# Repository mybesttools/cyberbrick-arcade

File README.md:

# ESP32-C3 Controller Firmware

This project targets **ESP32-C3 BLE gamepad mode** by default.

The board advertises as `ESP32-C3 Arcade` and pairs directly with RetroPie over Bluetooth.

It also includes an optional tiny OLED status display (SSD1306 I2C) showing:

- boot status
- advertising / connected state
- live axis and button activity

## BLE and USB support

Yes, both are supported from the same codebase:

- BLE gamepad mode on ESP32-C3 (`esp32c3_esp32c3_ble`)
- USB serial bridge mode on ESP32-C3 (`esp32c3_esp32c3_usbserial`)

Note: ESP32-C3 does not expose native USB HID gamepad device mode in this project.
USB mode here is CDC serial output for a Pi-side bridge.

## Project layout

- `src/main.cpp`: controller firmware (BLE + USB HID + serial bridge modes)
- `include/pinmap.h`: joystick/button mapping and calibration
- `platformio.ini`: PlatformIO build config
- `tools/flash_our_firmware.sh`: upload helper for default ESP32-C3 BLE env

## Pinouts

### Config B — single joystick, direct GPIO buttons (default)

Environments: `esp32c3_esp32c3_ble`, `esp32c3_esp32c3_usbserial`

**Joystick** (analog, connect to 3.3 V, GND, and wiper):

| Signal  | GPIO  | Arduino pin |
|---------|-------|-------------|
| JOY X   | GPIO0 | A0          |
| JOY Y   | GPIO1 | A1          |

**Buttons** (active LOW — wire between GPIO pin and GND, internal pull-up enabled):

| Button | GPIO |
|--------|------|
| A      | 2    |
| B      | 3    |
| X      | 4    |
| Y      | 5    |
| L      | 6    |
| R      | 7    |
| START  | 9    |
| SELECT | 10   |
| HOTKEY | 20   |
| COIN   | 21   |

**OLED status display** (I2C, shared with Config A):

| Signal | GPIO |
|--------|------|
| SDA    | 5    |
| SCL    | 6    |

> Note: GPIO5/6 are shared between the OLED and button Y/L in Config B.
> If the display is connected, remove buttons Y and L from the `BUTTON_PINS[]`
> array in `include/pinmap.h`, or remap them to unused GPIOs.

---

### Config A — dual joystick, MCP23017 expander board

Environments: `esp32c3_ble_mcp`

All buttons are wired to the MCP23017 I/O expander (no direct GPIO buttons).
The MCP23017 connects over I2C with A0/A1/A2 address pins all tied to GND
(address `0x20`).

**Joysticks** (analog, connect to 3.3 V, GND, and wiper):

| Signal       | GPIO  | Arduino pin | Role                  |
|--------------|-------|-------------|-----------------------|
| Left JOY X   | GPIO0 | A0          | Hat switch            |
| Left JOY Y   | GPIO1 | A1          | Hat switch            |
| Right JOY X  | GPIO2 | A2          | BLE Rx axis           |
| Right JOY Y  | GPIO3 | A3          | BLE Ry axis           |

**I2C bus** (MCP23017 + OLED share the same bus):

| Signal | GPIO | Connected to         |
|--------|------|----------------------|
| SDA    | 5    | MCP23017 SDA, OLED SDA |
| SCL    | 6    | MCP23017 SCL, OLED SCL |

**MCP23017 button mapping** (active LOW — wire each button between the
MCP pin and GND; internal pull-ups are enabled by firmware):

| MCP pin | Board label | Button | Notes |
|---------|-------------|--------|-------|
| GPA0    | A0          | D-pad Up    | ✓ wired |
| GPA1    | A1          | D-pad Left  | ✓ wired |
| GPA2    | A2          | D-pad Right | ✓ wired |
| GPA3    | A3          | D-pad Down  | ✓ wired |
| GPA4    | A4          | L shoulder  | wire here |
| GPA5    | A5          | R shoulder  | wire here |
| GPA6    | A6          | Start       | wire here |
| GPA7    | A7          | Select      | wire here |
| GPB0    | B0          | Hotkey      | wire here |
| GPB1    | B1          | Coin        | wire here |
| GPB2    | B2          | R3 (right joystick click) | ✓ wired |
| GPB3    | B3          | L3 (left joystick click)  | ✓ wired |
| GPB4    | B4          | A / Cross ✕   (Down)  | ✓ wired |
| GPB5    | B5          | Y / Triangle △ (Up)   | ✓ wired |
| GPB6    | B6          | B / Circle ○  (Right) | ✓ wired |
| GPB7    | B7          | X / Square □  (Left)  | ✓ wired |

## Optional tiny OLED display

The BLE environment enables status output (`ESP32C3_STATUS_OLED`).

For ABrobot ESP32-C3 OLED boards, the onboard 0.42" display is a 72x40 pixel
OLED driven over I2C on GPIO5 (SDA) / GPIO6 (SCL).

**Reference article:**
[ESP32-C3 0.42" OLED — emalliab](https://emalliab.wordpress.com/2025/02/12/esp32-c3-0-42-oled/)

Key findings from debugging:
- Board I2C address may be **0x3C** or **0x3D** depending on variant — firmware probes both.
- Display controller may be SSD1306 or SH1106 — both U8g2 drivers are included.
- `Wire.begin()` with no arguments on ESP32-C3 defaults to GPIO8/GPIO9, which
  conflicts with the onboard LED on GPIO8. Always pass explicit SDA/SCL pins.
- The article uses `U8G2_SSD1306_72X40_ER_F_HW_I2C` which works without offset.
  The `U8G2_SSD1306_128X64_NONAME` variant also works with offset (30, 12).

Default config is in `include/pinmap.h`:

- `STATUS_DISPLAY_ENABLED = false`
- `STATUS_OLED_I2C_ADDR = 0x3C`
- `STATUS_OLED_USE_SH1106_72X40 = true`
- `STATUS_OLED_SDA_PIN = 5`
- `STATUS_OLED_SCL_PIN = 6`

Note: ABrobot SH1106 72x40 panels are not SSD1306-compatible and need SH1106
command mode.

If your display has different dimensions or address, change those constants.

## Setup — step by step

### 1. Build and upload to ESP32-C3

```bash
cd firmware/esp32c3-usb-gamepad
pio run -e esp32c3_esp32c3_ble
pio run -e esp32c3_esp32c3_ble -t upload

# USB serial bridge firmware
pio run -e esp32c3_esp32c3_usbserial
pio run -e esp32c3_esp32c3_usbserial -t upload
```

If needed, upload with explicit port:

```bash
pio run -e esp32c3_esp32c3_ble -t upload --upload-port /dev/tty.usbmodemXXXX
```

Or use the helper script:

```bash
./tools/flash_our_firmware.sh
```

### 2. Pair with RetroPie

In RetroPie Bluetooth settings:

1. Register and connect new Bluetooth device
2. Select `ESP32-C3 Arcade`

### 3. Configure in EmulationStation

In RetroPie/EmulationStation:

1. Hold any button to start controller setup.
2. Map joystick directions and action buttons.
3. Map Start / Select / Hotkey.
4. Skip unused controls by holding a button.

## Verify on Pi (optional)

Install joystick tools to inspect Linux input events:

```bash
sudo apt install joystick
```

Test:

```bash
jstest /dev/input/js0
```

## Raspberry Pi OS and RetroPie setup

### Recommended OS: Raspberry Pi OS Lite (32-bit)

RetroPie runs its own EmulationStation frontend and does not need a desktop environment.
Lite keeps the install lean and leaves more RAM and CPU for emulation.

### 1. Flash the SD card

Use [Raspberry Pi Imager](https://www.raspberrypi.com/software/) on your Mac:

1. Choose **Raspberry Pi OS (other) → Raspberry Pi OS Lite (32-bit)**
2. Open the settings panel (gear icon) and configure:
   - Hostname (e.g. `retropie`)
   - Username and password
   - Wi-Fi SSID and password
   - **Enable SSH**
3. Flash to your SD card

> SSH is disabled by default on Raspberry Pi OS. Enabling it in Imager before flashing means you can connect headlessly from the first boot.

### 2. Install RetroPie

SSH in, then run:

```bash
sudo locale-gen en_US.UTF-8
sudo update-locale LC_ALL=en_US.UTF-8 LANG=en_US.UTF-8
sudo apt-get update && sudo apt-get upgrade -y
sudo apt-get install -y git
git clone --depth=1 https://github.com/RetroPie/RetroPie-Setup.git
cd RetroPie-Setup
sudo ./retropie_setup.sh
```

Choose **Basic Install** from the menu. Takes 30–60 minutes on a Pi 3 or 4.

---

## USB serial bridge — install and run from GitHub

On the Raspberry Pi, clone the repo, install the dependencies, and run the bridge script:

```bash
git clone https://github.com/mybesttools/esp32-c3-arcade.git
cd esp32-c3-arcade
sudo apt-get update
sudo apt install -y python3-serial python3-evdev
sudo python3 firmware/esp32-c3-usb-gamepad/tools/pi_usb_serial_to_uinput.py --port auto
```

To target a specific port instead:

```bash
sudo python3 firmware/esp32-c3-usb-gamepad/tools/pi_usb_serial_to_uinput.py --port /dev/ttyACM0
```

The script requires `sudo` to create a uinput virtual gamepad device.

### Install as a systemd service

This runs the bridge automatically on boot. Assumes the repo was cloned to `/home/admin/esp32-c3-arcade`.

Create the service file:

```bash
sudo tee /etc/systemd/system/esp32-gamepad-bridge.service > /dev/null << 'EOF'
[Unit]
Description=ESP32-C3 USB serial gamepad bridge
After=local-fs.target

[Service]
ExecStart=/usr/bin/python3 /home/admin/esp32-c3-arcade/firmware/esp32-c3-usb-gamepad/tools/pi_usb_serial_to_uinput.py --port auto
Restart=on-failure
RestartSec=5

[Install]
WantedBy=multi-user.target
EOF
```

Enable and start it:

```bash
sudo systemctl daemon-reload
sudo systemctl enable esp32-gamepad-bridge
sudo systemctl start esp32-gamepad-bridge
```

Check status:

```bash
sudo systemctl status esp32-gamepad-bridge
```

> If you cloned the repo to a different path, update `ExecStart` accordingly.

## Tuning

Edit `include/pinmap.h` and adjust:

- `JOY_CENTER_X`, `JOY_CENTER_Y`
- `JOY_DEADZONE`
- `JOY_MIN`, `JOY_MAX`
- `BUTTON_PINS[]` order if you want a different button layout

## Environments

| Environment | Config | Description |
|---|---|---|
| `esp32c3_esp32c3_ble` | B | BLE gamepad, single joystick, direct GPIO buttons (default) |
| `esp32c3_ble_mcp` | A | BLE gamepad, dual joystick, MCP23017 expander buttons |
| `esp32c3_esp32c3_usbserial` | B | USB CDC serial bridge for Pi-side uinput script, single joystick |
| `esp32c3_rp2040_usbhid` | — | Wired USB HID gamepad on Raspberry Pi Pico |

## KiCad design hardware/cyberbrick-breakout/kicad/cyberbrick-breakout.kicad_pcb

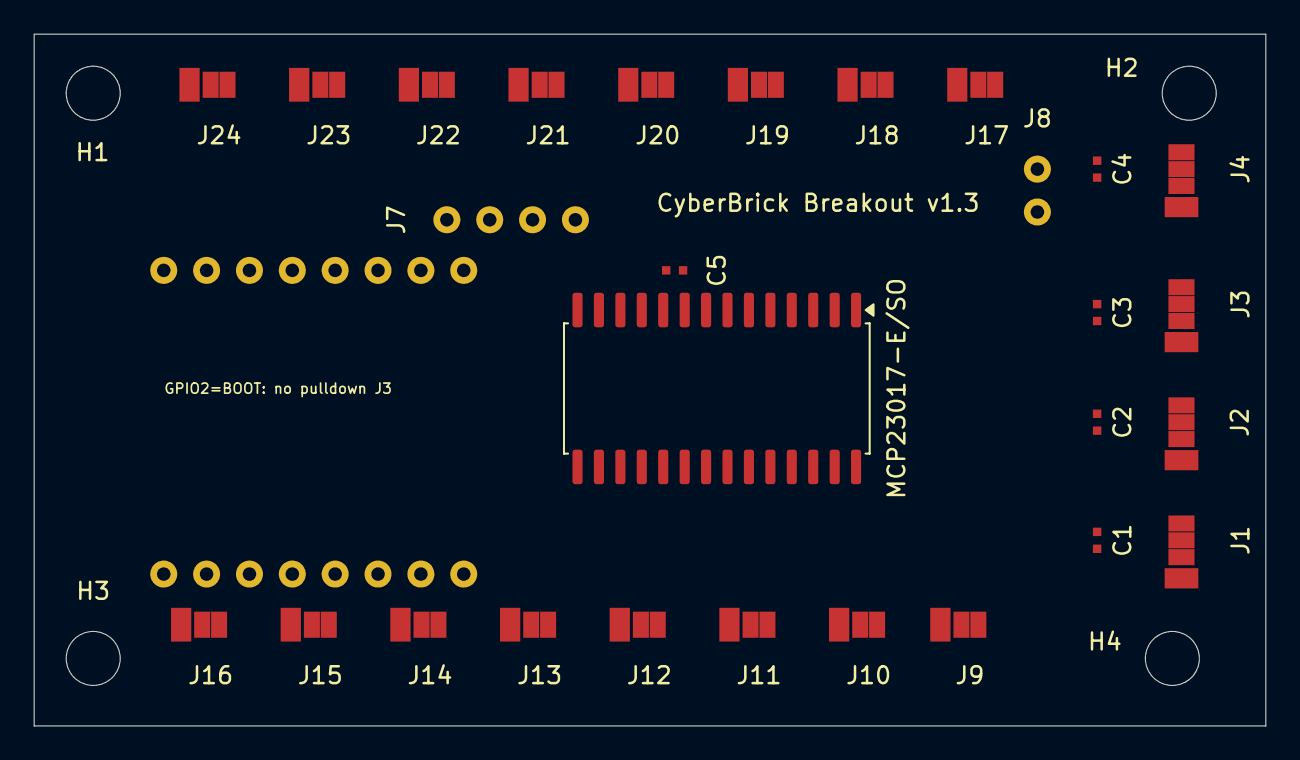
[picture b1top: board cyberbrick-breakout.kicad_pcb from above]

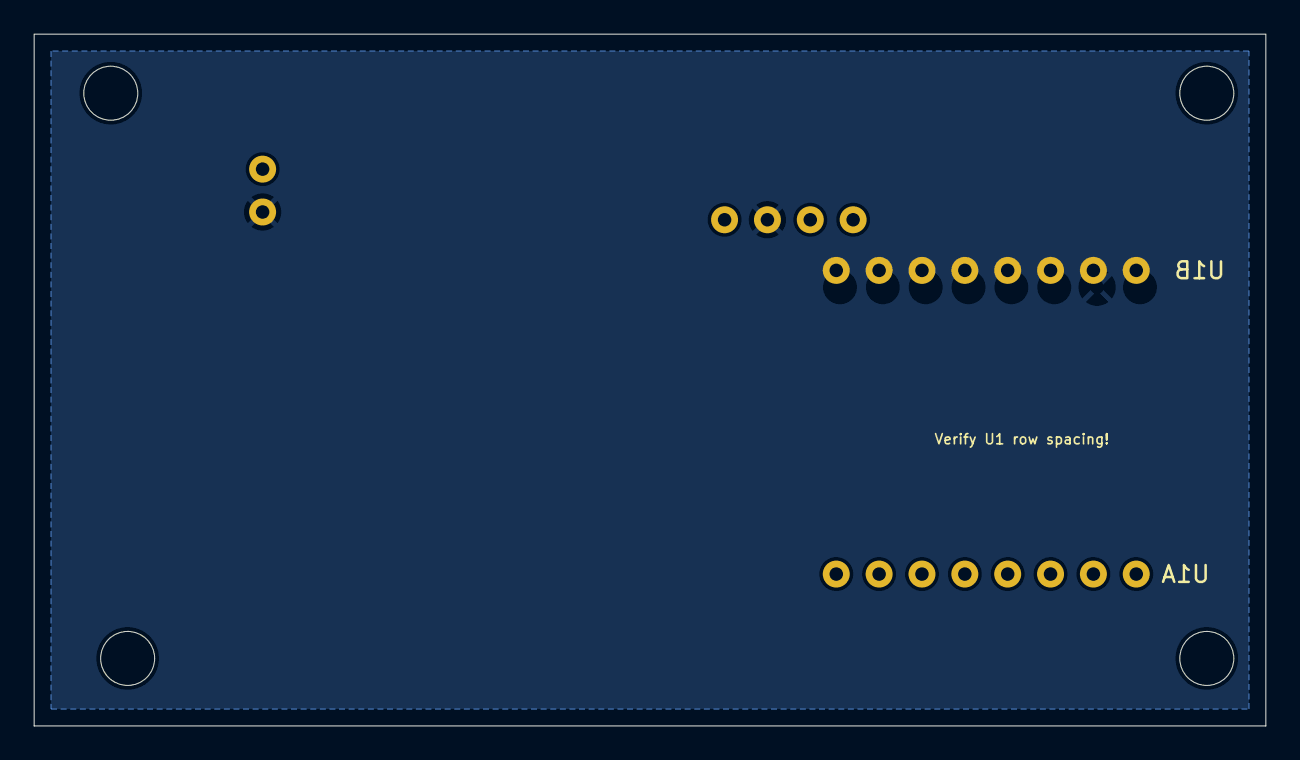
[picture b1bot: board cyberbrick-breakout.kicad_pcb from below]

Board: 2 copper layers, 73.0 x 41.0 mm, 34 parts (2 on the bottom side), 24 nets, no tracks yet.

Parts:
C1, C2, C3, C4, C5: 100nF; C_0402_1005Metric
H1, H2, H3, H4: M3; MountingHole_3.2mm_M3
J1: LX; JST_SH_SM03B-SRSS-TB_1x03-1MP_P1.00mm_Horizontal
J2: LY; JST_SH_SM03B-SRSS-TB_1x03-1MP_P1.00mm_Horizontal
J3: RX; JST_SH_SM03B-SRSS-TB_1x03-1MP_P1.00mm_Horizontal
J4: RY; JST_SH_SM03B-SRSS-TB_1x03-1MP_P1.00mm_Horizontal
J7: I2C; PinHeader_1x04_P2.54mm_Vertical
J8: PWR; PinHeader_1x02_P2.54mm_Vertical
J9: DL_UP; JST_SH_SM02B-SRSS-TB_1x02-1MP_P1.00mm_Horizontal
J10: DL_LFT; JST_SH_SM02B-SRSS-TB_1x02-1MP_P1.00mm_Horizontal
J11: DL_RGT; JST_SH_SM02B-SRSS-TB_1x02-1MP_P1.00mm_Horizontal
J12: DL_DWN; JST_SH_SM02B-SRSS-TB_1x02-1MP_P1.00mm_Horizontal
J13: DR_UP; JST_SH_SM02B-SRSS-TB_1x02-1MP_P1.00mm_Horizontal
J14: DR_LFT; JST_SH_SM02B-SRSS-TB_1x02-1MP_P1.00mm_Horizontal
J15: DR_RGT; JST_SH_SM02B-SRSS-TB_1x02-1MP_P1.00mm_Horizontal
J16: DR_DWN; JST_SH_SM02B-SRSS-TB_1x02-1MP_P1.00mm_Horizontal
J17: SHL1; JST_SH_SM02B-SRSS-TB_1x02-1MP_P1.00mm_Horizontal
J18: SHL2; JST_SH_SM02B-SRSS-TB_1x02-1MP_P1.00mm_Horizontal
J19: SHR1; JST_SH_SM02B-SRSS-TB_1x02-1MP_P1.00mm_Horizontal
J20: SHR2; JST_SH_SM02B-SRSS-TB_1x02-1MP_P1.00mm_Horizontal
J21: START; JST_SH_SM02B-SRSS-TB_1x02-1MP_P1.00mm_Horizontal
J22: SEL; JST_SH_SM02B-SRSS-TB_1x02-1MP_P1.00mm_Horizontal
J23: HOTKEY; JST_SH_SM02B-SRSS-TB_1x02-1MP_P1.00mm_Horizontal
J24: COIN; JST_SH_SM02B-SRSS-TB_1x02-1MP_P1.00mm_Horizontal
MCP23017-E/SO: SOIC-28W_7.5x17.9mm_P1.27mm
U1A: ESP32-C3 top; PinSocket_1x08_P2.54mm_Vertical
U1B: ESP32-C3 bot; PinSocket_1x08_P2.54mm_Vertical

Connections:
ADC_LX: J1.2, U1B.8
ADC_LY: J2.2, U1B.7
ADC_RX: J3.2, U1B.6
ADC_RY: J4.2, U1A.8
BTN_COIN: J24.1, MCP23017-E/SO.8
BTN_DL_DOWN: J12.1, MCP23017-E/SO.24
BTN_DL_LEFT: J10.1, MCP23017-E/SO.22
BTN_DL_RIGHT: J11.1, MCP23017-E/SO.23
BTN_DL_UP: J9.1, MCP23017-E/SO.21
BTN_DR_DOWN: J16.1, MCP23017-E/SO.28
BTN_DR_LEFT: J14.1, MCP23017-E/SO.26
BTN_DR_RIGHT: J15.1, MCP23017-E/SO.27
BTN_DR_UP: J13.1, MCP23017-E/SO.25
BTN_HOTKEY: J23.1, MCP23017-E/SO.7
BTN_SELECT: J22.1, MCP23017-E/SO.6
BTN_SHL1: J17.1, MCP23017-E/SO.1
BTN_SHL2: J18.1, MCP23017-E/SO.2
BTN_SHR1: J19.1, MCP23017-E/SO.3
BTN_SHR2: J20.1, MCP23017-E/SO.4
BTN_START: J21.1, MCP23017-E/SO.5
GND: C1.2, C2.2, C3.2, C4.2, C5.1, J1.3, J2.3, J3.3, J4.3, J7.3, J8.2, J9.2, J10.2, J11.2, J12.2, J13.2, J14.2, J15.2, J16.2, J17.2, J18.2, J19.2, J20.2, J21.2, J22.2, J23.2, J24.2, MCP23017-E/SO.10, MCP23017-E/SO.15, MCP23017-E/SO.16, MCP23017-E/SO.17, U1B.2
I2C_SCL: J7.2, MCP23017-E/SO.12, U1A.5
I2C_SDA: J7.1, MCP23017-E/SO.13, U1A.6
VCC: C1.1, C2.1, C3.1, C4.1, C5.2, J1.1, J2.1, J3.1, J4.1, J7.4, J8.1, MCP23017-E/SO.9, MCP23017-E/SO.18, U1B.3

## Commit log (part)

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2026-04-19 Remove .pio build artifacts from tracking
    These were committed before .gitignore was added. Files remain
    on disk but are no longer tracked by git.
2026-04-27 moved readme
2026-05-05 Add generated PCB layout for CyberBrick breakout v1.2
    - cyberbrick-breakout.kicad_pcb: KiCad 7/8 PCB, 85x70mm
    - ABrobot ESP32-C3 OLED module socket (2x 1x8 female, centred)
    - 4x SH1.0 3-pin joystick connectors (SM03B-SRSS-TB) along top edge
    - 16x SH1.0 2-pin button connectors (SM02B-SRSS-TB) along bottom edge
    - J6 MCP23017 2x9 button header, right edge
    - J7 I2C 1x4 header, right edge
2026-05-05 Fix KiCad layer table: use correct layer numbers and names (F.CrtYd, B.CrtYd, F.Fab, B.Fab)
2026-05-05 Fix U1 socket orientation: angle 90 so rows are horizontal, correct pin1 positions
2026-05-06 Minor changes
